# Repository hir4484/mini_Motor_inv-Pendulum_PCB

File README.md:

車輪型(2輪)倒立振子の製作ファイル

ここは、倒立振子の制御基板(回路CAD)ファイル、のリポジトリとなります。

This is a repository for inverted pendulum control board (circuit CAD) files.

//

製作内容は、下記youtubeをご参照下さい。

Please refer to the YouTube link below for details of the production.

https://www.youtube.com/watch?v=W9z1Mw9BegU

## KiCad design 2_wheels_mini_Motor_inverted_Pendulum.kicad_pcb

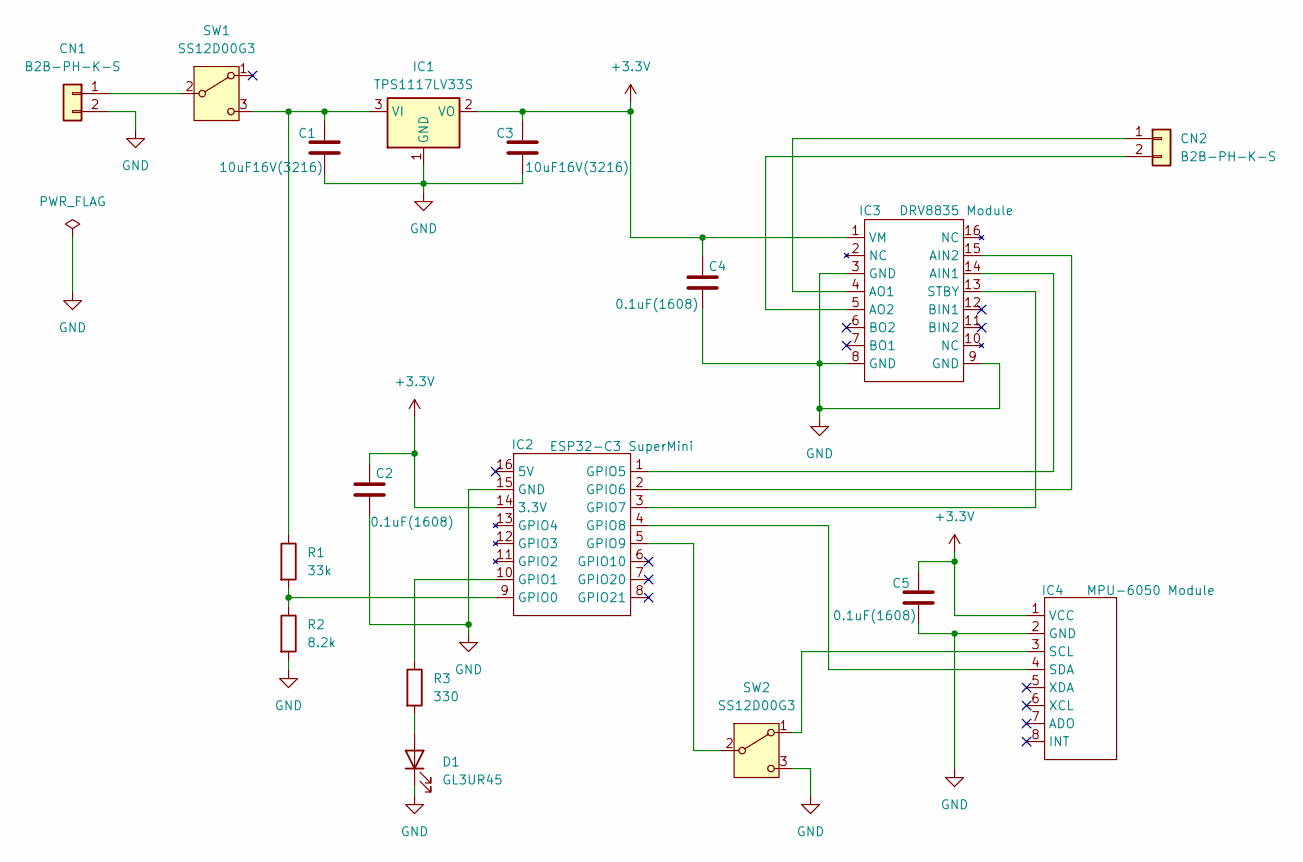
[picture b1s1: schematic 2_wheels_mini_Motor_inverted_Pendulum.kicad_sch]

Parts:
C1, C3: 10uF16V(3216); C_1206_3216Metric_Pad1.33x1.80mm_HandSolder
C2, C4, C5: 0.1uF(1608); C_0603_1608Metric_Pad1.08x0.95mm_HandSolder
CN1, CN2: B2B-PH-K-S; JST_PH_B2B-PH-K_1x02_P2.00mm_Vertical
D1: GL3UR45; LED_D3.0mm
IC1: TPS1117LV33S; SOT-223-3_TabPin2
IC2: ESP32-C3 SuperMini
IC3: DRV8835 Module; ESP32-C3 SuperMini
IC4: MPU-6050 Module
R1: 33k; R_Axial_DIN0204_L3.6mm_D1.6mm_P5.08mm_Horizontal
R2: 8.2k; R_Axial_DIN0204_L3.6mm_D1.6mm_P5.08mm_Horizontal
R3: 330; R_Axial_DIN0204_L3.6mm_D1.6mm_P5.08mm_Horizontal
SW1, SW2: SS12D00G3; PinHeader_3_P2.00_d0.8

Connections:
+3.3V: C2.1, C3.1, C4.1, C5.1, IC1.2 (VO), IC2.14 (3.3V), IC3.1 (VM), IC4.1 (VCC)
GND: C1.2, C2.2, C3.2, C4.2, C5.2, CN1.2, D1.1 (K), IC1.1 (GND), IC2.15 (GND), IC3.3 (GND), IC3.8 (GND), IC3.9 (GND), IC4.2 (GND), R2.2, SW2.3 (C)
unnamed: CN1.1, SW1.2 (B)
unnamed: CN2.1, IC3.4 (AO1)
unnamed: CN2.2, IC3.5 (AO2)
unnamed: D1.2 (A), R3.2
unnamed: C1.1, IC1.3 (VI), R1.1, SW1.3 (C)
unnamed: IC2.9 (GPIO0), R1.2, R2.1
unnamed: IC2.10 (GPIO1), R3.1
unnamed: IC2.1 (GPIO5), IC3.14 (AIN1)
unnamed: IC2.2 (GPIO6), IC3.15 (AIN2)
unnamed: IC2.3 (GPIO7), IC3.13 (STBY)
unnamed: IC2.4 (GPIO8), IC4.4 (SDA)
unnamed: IC2.5 (GPIO9), SW2.2 (B)
unnamed: IC4.3 (SCL), SW2.1 (A)

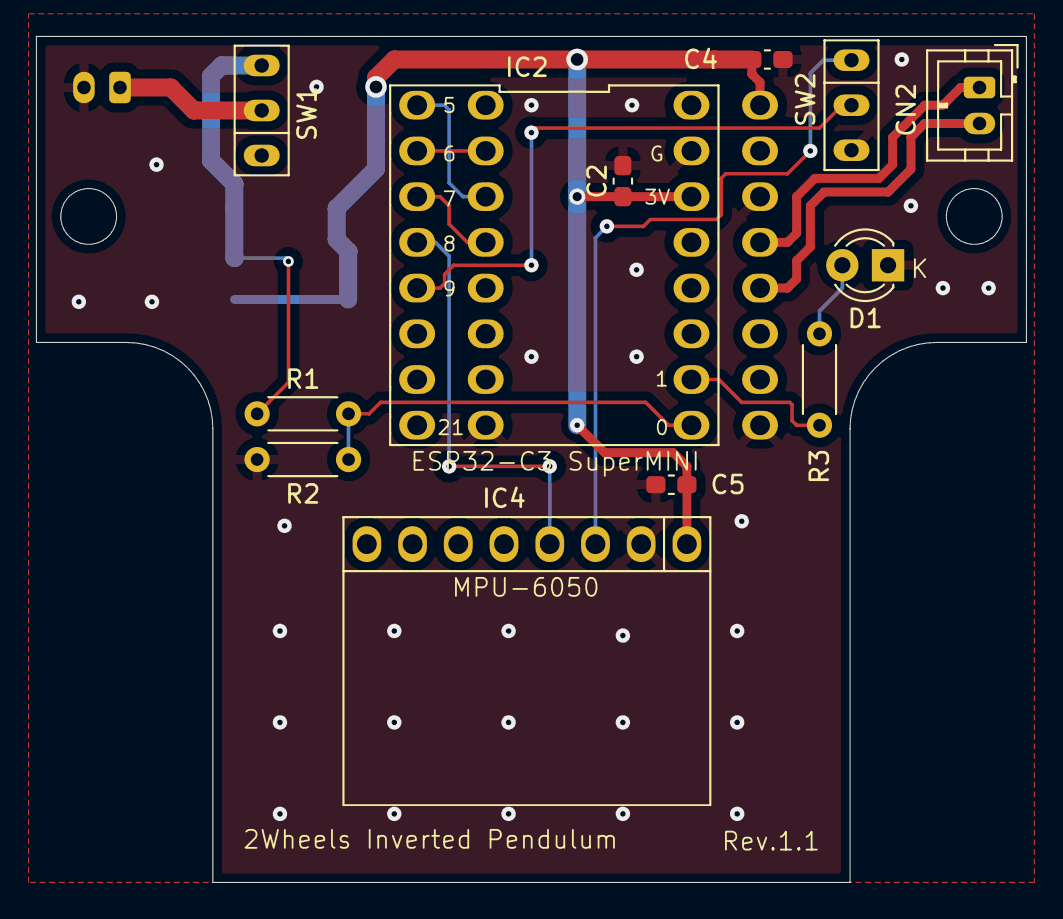
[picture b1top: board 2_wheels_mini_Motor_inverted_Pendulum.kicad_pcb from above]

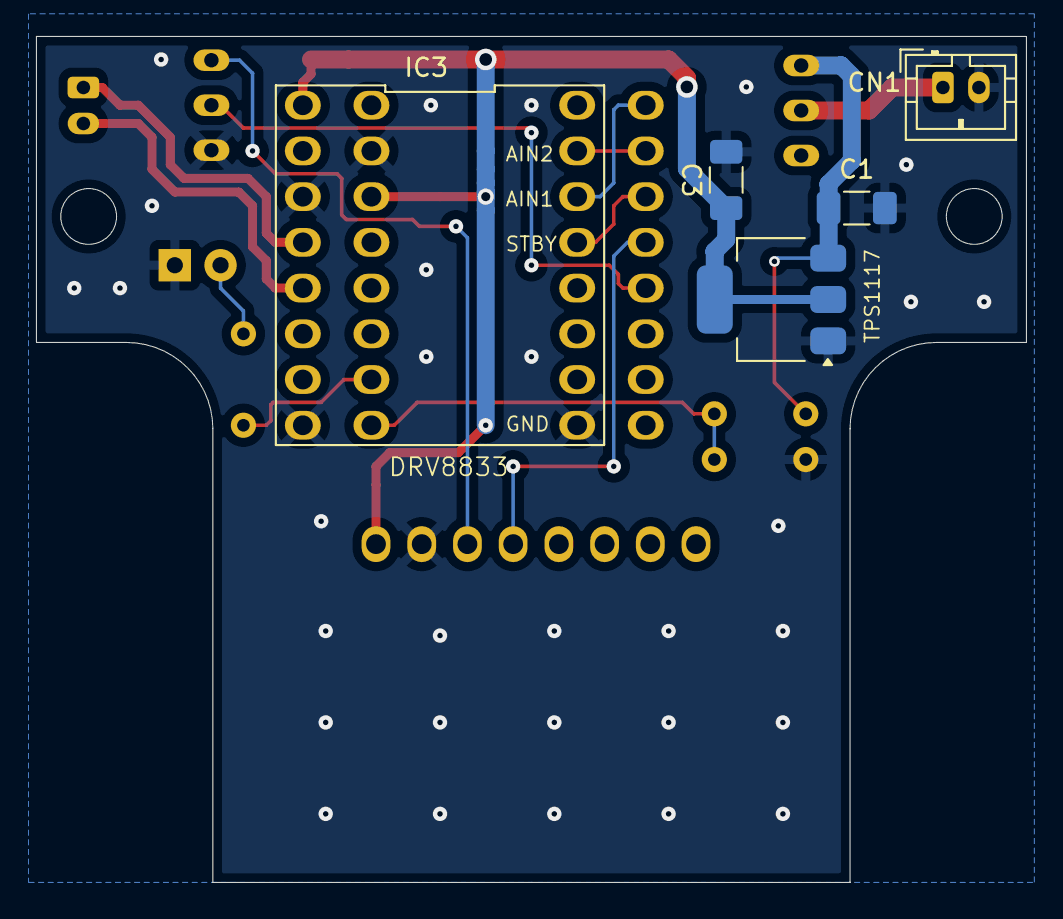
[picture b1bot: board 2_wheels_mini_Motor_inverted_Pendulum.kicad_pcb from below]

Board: 2 copper layers, 55.0 x 47.0 mm, 17 parts (5 on the bottom side), 15 nets.

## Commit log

2025-04-13 KiCAD file
2025-04-13 gerber file
2025-04-13 pic file
